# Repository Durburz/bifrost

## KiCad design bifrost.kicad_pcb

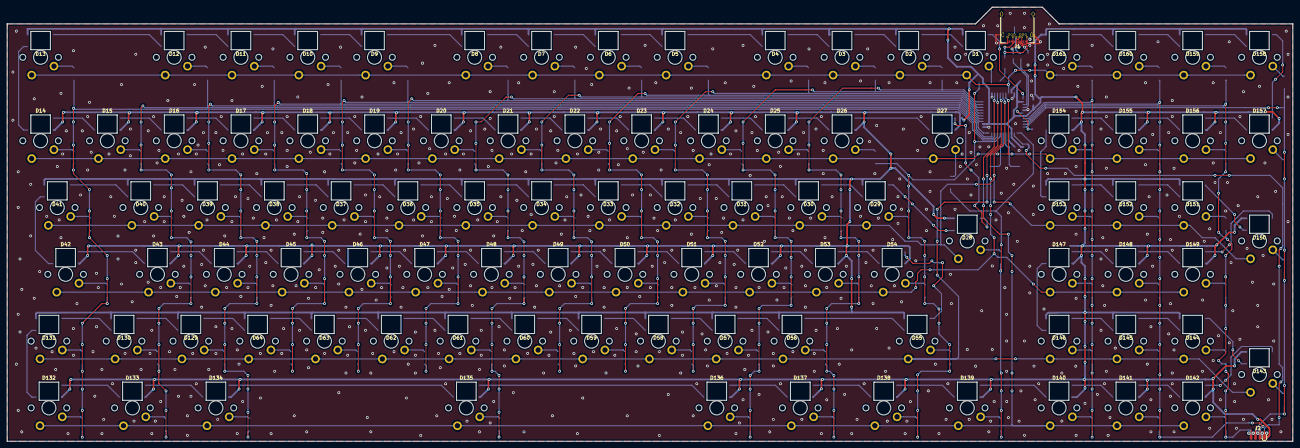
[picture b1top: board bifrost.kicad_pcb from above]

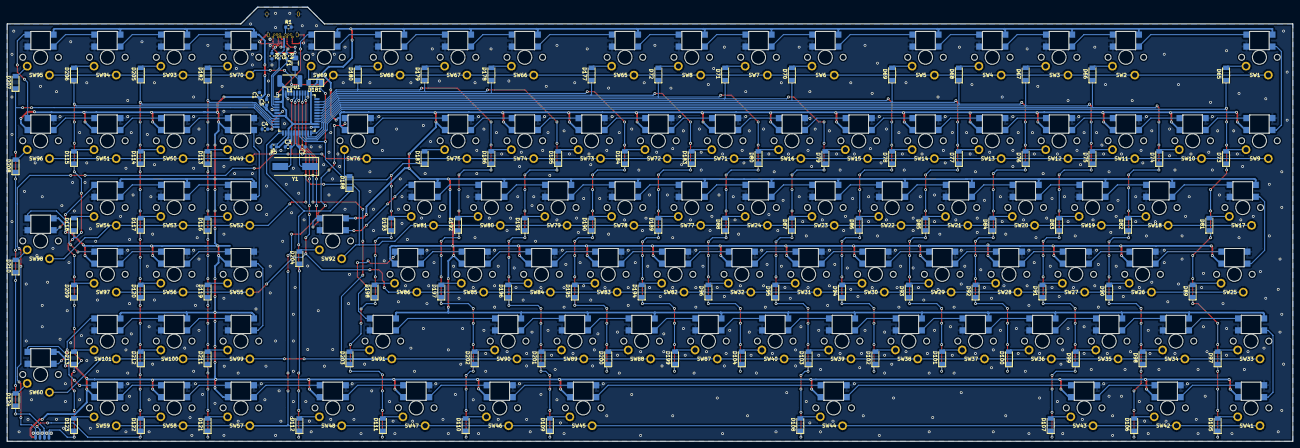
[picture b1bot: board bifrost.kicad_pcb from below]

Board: 2 copper layers, 366.7 x 123.8 mm, 307 parts (208 on the bottom side), 232 nets.

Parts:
C1: 10µ; C_0603_1608Metric
C2, C3: 22p; C_0603_1608Metric
C4: 1µ; C_0603_1608Metric
C5: 100n; C_0603_1608Metric
D1, D2, D3, D4, D5, D6, D7, D8, D9, D10, D11, D12, D13, D14, D15, D16, D17, D18, D19, D20, D21, D22, D23, D24, D25, D26, D27, D28, D29, D30, D31, D32, D33, D34, D35, D36, D37, D38, D39, D40, D41, D42, D43, D44, D45, D46, D47, D48, D49, D50, D51, D52, D53, D54, D55, D56, D57, D58, D59, D60, D61, D62, D63, D64, D129, D130, D131, D132, D133, D134, D135, D136, D137, D138, D139, D140, D141, D142, D143, D144, D145, D146, D147, D148, D149, D150, D151, D152, D153, D154, D155, D156, D157, D158, D159, D160, D161: SK6812; SK6812_IN-PCB
D65, D66, D67, D68, D69, D70, D71, D72, D73, D74, D75, D76, D77, D78, D79, D80, D81, D82, D83, D84, D85, D86, D87, D88, D89, D90, D91, D92, D93, D94, D95, D96, D97, D98, D99, D100, D101, D102, D103, D104, D105, D106, D107, D108, D109, D110, D111, D112, D113, D114, D115, D116, D117, D118, D119, D120, D121, D122, D123, D124, D177, D178, D179, D180, D181, D182, D183, D184, D185, D186, D187, D188, D189, D190, D191, D192, D193, D194, D195, D196, D197, D198, D199, D200, D201, D202, D203, D204, D205, D206, D207, D208, D209, D210, D211, D212, D213: D; D_MiniMELF
F1: 500mA; Fuse_1206_3216Metric_Pad1.42x1.75mm_HandSolder
J1: USB_C_Receptacle; USB_C_Receptacle_Amphenol_12401548E4-2A
J2: Conn_02x04_Counter_Clockwise; SOIC_clipProgSmall
L1: 80R; L_2512_6332Metric
R1, R2: 5K1; R_0603_1608Metric
R3, R4: 22R; R_0603_1608Metric
R5: 10K; R_0603_1608Metric
SW1, SW2, SW3, SW4, SW5, SW6, SW7, SW8, SW9, SW10, SW11, SW12, SW13, SW14, SW15, SW16, SW17, SW18, SW19, SW20, SW21, SW22, SW23, SW24, SW25, SW26, SW27, SW28, SW29, SW30, SW31, SW32, SW33, SW34, SW35, SW36, SW37, SW38, SW39, SW40, SW41, SW42, SW43, SW44, SW45, SW46, SW47, SW48, SW49, SW50, SW51, SW52, SW53, SW54, SW55, SW56, SW57, SW58, SW59, SW60, SW65, SW66, SW67, SW68, SW69, SW70, SW71, SW72, SW73, SW74, SW75, SW76, SW77, SW78, SW79, SW80, SW81, SW82, SW83, SW84, SW85, SW86, SW87, SW88, SW89, SW90, SW91, SW92, SW93, SW94, SW95, SW96, SW97, SW98, SW99, SW100, SW101: SW_SPST; CHERRY-MX_simple
U1: ATmega32U4-AU; TQFP-44_10x10mm_P0.8mm
Y1: 16MHZ; Crystal_SMD_HC49-SD

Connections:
1: D65.1, D73.1, D81.1, D89.1, D97.1, D105.1, U1.19
2: D66.1, D74.1, D82.1, D90.1, D98.1, D106.1, U1.20
3: D67.1, D75.1, D83.1, D91.1, D99.1, D107.1, U1.21
4: D68.1, D76.1, D84.1, D92.1, D100.1, U1.22
5: D69.1, D77.1, D85.1, D93.1, D101.1, U1.25
6: D70.1, D78.1, D86.1, D94.1, D102.1, U1.26
7: D71.1, D79.1, D87.1, D95.1, D103.1, D108.1, U1.27
8: D72.1, D80.1, D88.1, D96.1, D104.1, U1.28
9: D177.1, D183.1, D189.1, D194.1, D199.1, U1.29
10: D178.1, D184.1, D190.1, D195.1, D200.1, U1.30
11: D109.1, D179.1, D185.1, D191.1, D196.1, D201.1, U1.31
12: D110.1, D180.1, D186.1, D192.1, D197.1, D202.1, U1.32
13: D111.1, D181.1, D187.1, D193.1, D198.1, D203.1, U1.18
14: D112.1, D188.1, D204.1, U1.12
15: D113.1, D116.1, D119.1, D121.1, D182.1, D211.1, U1.8
16: D114.1, D117.1, D120.1, D122.1, D205.1, D212.1, J2.7, U1.9
17: D115.1, D118.1, D123.1, D206.1, D209.1, D213.1, J2.5, U1.10
18: D124.1, D207.1, D208.1, D210.1, J2.6, U1.11
+5V: C1.1, C5.1, D1.3, D2.3, D3.3, D4.3, D5.3, D6.3, D7.3, D8.3, D9.3, D10.3, D11.3, D12.3, D13.3, D14.3, D15.3, D16.3, D17.3, D18.3, D19.3, D20.3, D21.3, D22.3, D23.3, D24.3, D25.3, D26.3, D27.3, D28.3, D29.3, D30.3, D31.3, D32.3, D33.3, D34.3, D35.3, D36.3, D37.3, D38.3, D39.3, D40.3, D41.3, D42.3, D43.3, D44.3, D45.3, D46.3, D47.3, D48.3, D49.3, D50.3, D51.3, D52.3, D53.3, D54.3, D55.3, D56.3, D57.3, D58.3, D59.3, D60.3, D61.3, D62.3, D63.3, D64.3, D129.3, D130.3, D131.3, D132.3, D133.3, D134.3, D135.3, D136.3, D137.3, D138.3, D139.3, D140.3, D141.3, D142.3, D143.3, D144.3, D145.3, D146.3, D147.3, D148.3, D149.3, D150.3, D151.3, D152.3, D153.3, D154.3, D155.3, D156.3, D157.3, D158.3, D159.3, D160.3, D161.3, J2.1, L1.2, R5.1, U1.2, U1.7, U1.14, U1.24, U1.34, U1.42, U1.44
A: SW1.1, SW2.1, SW3.1, SW4.1, SW5.1, SW6.1, SW7.1, SW8.1, SW65.1, SW66.1, SW67.1, SW68.1, SW69.1, SW70.1, SW93.1, SW94.1, SW95.1, U1.41
B: SW9.1, SW10.1, SW11.1, SW12.1, SW13.1, SW14.1, SW15.1, SW16.1, SW49.1, SW50.1, SW51.1, SW71.1, SW72.1, SW73.1, SW74.1, SW75.1, SW76.1, SW96.1, U1.40
C: SW17.1, SW18.1, SW19.1, SW20.1, SW21.1, SW22.1, SW23.1, SW24.1, SW52.1, SW53.1, SW54.1, SW77.1, SW78.1, SW79.1, SW80.1, SW81.1, SW92.1, SW98.1, U1.39
D: SW25.1, SW26.1, SW27.1, SW28.1, SW29.1, SW30.1, SW31.1, SW32.1, SW55.1, SW56.1, SW82.1, SW83.1, SW84.1, SW85.1, SW86.1, SW97.1, U1.38
DIN_LED: D1.2, U1.1
E: SW33.1, SW34.1, SW35.1, SW36.1, SW37.1, SW38.1, SW39.1, SW40.1, SW60.1, SW87.1, SW88.1, SW89.1, SW90.1, SW91.1, SW99.1, SW100.1, SW101.1, U1.37
F: SW41.1, SW42.1, SW43.1, SW44.1, SW45.1, SW46.1, SW47.1, SW48.1, SW57.1, SW58.1, SW59.1, U1.36
GND: C1.2, C2.1, C3.1, C4.1, C5.2, D1.1, D2.1, D3.1, D4.1, D5.1, D6.1, D7.1, D8.1, D9.1, D10.1, D11.1, D12.1, D13.1, D14.1, D15.1, D16.1, D17.1, D18.1, D19.1, D20.1, D21.1, D22.1, D23.1, D24.1, D25.1, D26.1, D27.1, D28.1, D29.1, D30.1, D31.1, D32.1, D33.1, D34.1, D35.1, D36.1, D37.1, D38.1, D39.1, D40.1, D41.1, D42.1, D43.1, D44.1, D45.1, D46.1, D47.1, D48.1, D49.1, D50.1, D51.1, D52.1, D53.1, D54.1, D55.1, D56.1, D57.1, D58.1, D59.1, D60.1, D61.1, D62.1, D63.1, D64.1, D129.1, D130.1, D131.1, D132.1, D133.1, D134.1, D135.1, D136.1, D137.1, D138.1, D139.1, D140.1, D141.1, D142.1, D143.1, D144.1, D145.1, D146.1, D147.1, D148.1, D149.1, D150.1, D151.1, D152.1, D153.1, D154.1, D155.1, D156.1, D157.1, D158.1, D159.1, D160.1, D161.1, J1.A1, J1.A12, J1.B1, J1.B12, J1.S1, J2.4, R1.2, R2.2, U1.5, U1.15, U1.23, U1.35, U1.43
unnamed: C2.2, U1.17, Y1.1
unnamed: C3.2, U1.16, Y1.2
unnamed: C4.2, U1.6
unnamed: D1.4, D2.2
unnamed: D2.4, D3.2
unnamed: D3.4, D4.2
unnamed: D4.4, D5.2
unnamed: D5.4, D6.2
unnamed: D6.4, D7.2
unnamed: D7.4, D8.2
unnamed: D8.4, D9.2
unnamed: D9.4, D10.2
unnamed: D10.4, D11.2
unnamed: D11.4, D12.2
unnamed: D12.4, D13.2
unnamed: D13.4, D14.2
unnamed: D14.4, D15.2
unnamed: D15.4, D16.2
unnamed: D16.4, D17.2
unnamed: D17.4, D18.2
unnamed: D18.4, D19.2
unnamed: D19.4, D20.2
unnamed: D20.4, D21.2
unnamed: D21.4, D22.2
unnamed: D22.4, D23.2
unnamed: D23.4, D24.2
unnamed: D24.4, D25.2
unnamed: D25.4, D26.2
unnamed: D26.4, D27.2
unnamed: D27.4, D28.2
unnamed: D28.4, D29.2
unnamed: D29.4, D30.2
unnamed: D30.4, D31.2
unnamed: D31.4, D32.2
unnamed: D32.4, D33.2
unnamed: D33.4, D34.2
unnamed: D34.4, D35.2
unnamed: D35.4, D36.2
unnamed: D36.4, D37.2
unnamed: D37.4, D38.2
unnamed: D38.4, D39.2
unnamed: D39.4, D40.2
unnamed: D40.4, D41.2
unnamed: D41.4, D42.2
unnamed: D42.4, D43.2
unnamed: D43.4, D44.2
unnamed: D44.4, D45.2
unnamed: D45.4, D46.2
unnamed: D46.4, D47.2
unnamed: D47.4, D48.2
unnamed: D48.4, D49.2
unnamed: D49.4, D50.2
unnamed: D50.4, D51.2
unnamed: D51.4, D52.2
unnamed: D52.4, D53.2
unnamed: D53.4, D54.2
unnamed: D54.4, D55.2
unnamed: D55.4, D56.2
unnamed: D56.4, D57.2
unnamed: D57.4, D58.2
unnamed: D58.4, D59.2
unnamed: D59.4, D60.2
unnamed: D60.4, D61.2
unnamed: D61.4, D62.2
unnamed: D62.4, D63.2
unnamed: D63.4, D64.2
unnamed: D65.2, SW1.2
unnamed: D66.2, SW2.2
unnamed: D67.2, SW3.2
unnamed: D68.2, SW4.2
unnamed: D69.2, SW5.2
unnamed: D70.2, SW6.2
unnamed: D71.2, SW7.2
unnamed: D72.2, SW8.2
unnamed: D73.2, SW9.2
unnamed: D74.2, SW10.2
unnamed: D75.2, SW11.2
unnamed: D76.2, SW12.2
unnamed: D77.2, SW13.2
unnamed: D78.2, SW14.2
unnamed: D79.2, SW15.2
unnamed: D80.2, SW16.2
unnamed: D81.2, SW17.2
unnamed: D82.2, SW18.2
unnamed: D83.2, SW19.2
unnamed: D84.2, SW20.2
unnamed: D85.2, SW21.2
unnamed: D86.2, SW22.2
unnamed: D87.2, SW23.2
unnamed: D88.2, SW24.2
unnamed: D89.2, SW25.2
unnamed: D90.2, SW26.2
unnamed: D91.2, SW27.2
unnamed: D92.2, SW28.2
unnamed: D93.2, SW29.2
unnamed: D94.2, SW30.2
unnamed: D95.2, SW31.2
unnamed: D96.2, SW32.2
unnamed: D97.2, SW33.2
unnamed: D98.2, SW34.2
unnamed: D99.2, SW35.2
unnamed: D100.2, SW36.2
unnamed: D101.2, SW37.2
unnamed: D102.2, SW38.2
unnamed: D103.2, SW39.2
unnamed: D104.2, SW40.2
unnamed: D105.2, SW41.2
unnamed: D106.2, SW42.2
unnamed: D107.2, SW43.2
unnamed: D108.2, SW44.2
unnamed: D109.2, SW45.2
unnamed: D110.2, SW46.2
unnamed: D111.2, SW47.2
unnamed: D112.2, SW48.2
unnamed: D113.2, SW49.2
unnamed: D114.2, SW50.2
unnamed: D115.2, SW51.2
unnamed: D116.2, SW52.2
unnamed: D117.2, SW53.2
unnamed: D118.2, SW54.2
unnamed: D119.2, SW55.2
unnamed: D120.2, SW56.2
unnamed: D121.2, SW57.2
unnamed: D122.2, SW58.2
unnamed: D123.2, SW59.2
unnamed: D124.2, SW60.2
unnamed: D64.4, D129.2
unnamed: D129.4, D130.2
unnamed: D130.4, D131.2
unnamed: D131.4, D132.2
unnamed: D132.4, D133.2
unnamed: D133.4, D134.2
unnamed: D134.4, D135.2
unnamed: D135.4, D136.2
unnamed: D136.4, D137.2
unnamed: D137.4, D138.2
unnamed: D138.4, D139.2
unnamed: D139.4, D140.2
unnamed: D140.4, D141.2
unnamed: D141.4, D142.2
unnamed: D142.4, D143.2
unnamed: D143.4, D144.2
unnamed: D144.4, D145.2
unnamed: D145.4, D146.2
unnamed: D146.4, D147.2
unnamed: D147.4, D148.2
unnamed: D148.4, D149.2
unnamed: D149.4, D150.2
unnamed: D150.4, D151.2
unnamed: D151.4, D152.2
unnamed: D152.4, D153.2
unnamed: D153.4, D154.2
unnamed: D154.4, D155.2
unnamed: D155.4, D156.2
unnamed: D156.4, D157.2
unnamed: D157.4, D158.2
unnamed: D158.4, D159.2
unnamed: D159.4, D160.2
unnamed: D160.4, D161.2
unnamed: D177.2, SW65.2
unnamed: D178.2, SW66.2
unnamed: D179.2, SW67.2
unnamed: D180.2, SW68.2
unnamed: D181.2, SW69.2
unnamed: D182.2, SW70.2
unnamed: D183.2, SW71.2
unnamed: D184.2, SW72.2
unnamed: D185.2, SW73.2
unnamed: D186.2, SW74.2
unnamed: D187.2, SW75.2
unnamed: D188.2, SW76.2
unnamed: D189.2, SW77.2
unnamed: D190.2, SW78.2
unnamed: D191.2, SW79.2
unnamed: D192.2, SW80.2
unnamed: D193.2, SW81.2
unnamed: D194.2, SW82.2
unnamed: D195.2, SW83.2
unnamed: D196.2, SW84.2
unnamed: D197.2, SW85.2
unnamed: D198.2, SW86.2
unnamed: D199.2, SW87.2
unnamed: D200.2, SW88.2
unnamed: D201.2, SW89.2
unnamed: D202.2, SW90.2
unnamed: D203.2, SW91.2
unnamed: D204.2, SW92.2
unnamed: D205.2, SW93.2
unnamed: D206.2, SW94.2
unnamed: D207.2, SW95.2
unnamed: D208.2, SW96.2
unnamed: D209.2, SW97.2
unnamed: D210.2, SW98.2
unnamed: D211.2, SW99.2
unnamed: D212.2, SW100.2
unnamed: D213.2, SW101.2
unnamed: F1.1, L1.1
unnamed: F1.2, J1.A4, J1.A9, J1.B4, J1.B9
unnamed: J1.A5, R2.1
unnamed: J1.A6, J1.B6, R3.1
unnamed: J1.A7, J1.B7, R4.1
unnamed: J1.B5, R1.1
unnamed: J2.8, R5.2, U1.13
unnamed: R3.2, U1.4
unnamed: R4.2, U1.3

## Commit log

2018-10-19 added project and digikey lib
2018-10-19 added libs
2018-10-27 basic schematic
2018-10-27 daughterboard connector
2018-10-27 Add LICENSE
2018-11-01 added led passthrough
2018-11-01 minor improvements
2020-01-29 edit schematic an basic button placing
2020-01-31 save before diddelidoo
2020-02-01 complete makeover
2020-02-02 rev0
